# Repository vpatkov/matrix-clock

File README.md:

# Matrix Clock with Weather Station

Not too small, not too big, auto-syncing clock with wide viewing angle,
pretty bright at sunny day and not too bright at night, having a
simple weather station, without any wires except a Micro-USB power.

- Show clock, outdoor and indoor temperatures, indoor relative humidity, and
  atmospheric pressure
- Show the peak values and the change of any weather parameter for 24 hours
- Clock is wirelessly synced with a PC and maintained when the PC is offline
- Automatic brightness control
- Intuitively controlled with a single clickable rotary encoder on the back side

The project includes a base station with a LED matrix display, and two
wireless modules: one is for measuring outdoor temperature, and one is for
communication with a PC (syncing time).

If, for some reason, the base station conclude that some data is unreliable, it
show the latest reliable data with a warning mark as a point in the bottom
right corner. Clock is unreliable if not synced with a PC for a week. Outdoor
temperature is unreliable if no data was received from the outdoor sensor for
10 minutes. Data from indoor sensors is unreliable in case of any error.

If the battery in the outdoor module is low, a warning mark as a point in
the top right corner appears on the outdoor temperature screen.

It's a project I made for personal use in 2014 with some updates then.
It's based on my own preferences and ad hoc decisions. Also, it's my first
real-world electronic project after "LED blinking", and so have many design
lacks.

## Technical details

The base station is a sandwich of two boards called in sources as `base` and
`matrix`. The `base` board contains an MCU, indoor sensors, RF module, and other
peripherals. The `matrix` board is just a SPI controlled 24×8 LED matrix.

The wireless modules are called in sources as `outdoor` (outdoor temperature
measurement) and `pc-link` (communication with a PC). The `pc-link` module
is connected to a PC by USB, and appears as a virtual serial port (CP2102N chip
is used for that). CP2102N also feeds 1 MHz clock to the MCU, the chip
must be configured for that with Silabs' [configuration tool](https://www.silabs.com/products/development-tools/software/simplicity-studio).
The `pc-link` module is controlled by a host program `matrix-clock` (in the
`software` directory). Currently, the program is used just for sending
current time to the base station (add it to cron).

The wireless network is build on Nordic NRF24L01+ chips.

The front and rear glasses for the base station are made in
[Ponoko](https://www.ponoko.com/) by laser cutting from "acrylic gray tint"
material using the `case/base-station.svg` file.

The case for the outdoor module is 3D printed from the `case/outdoor-case.stl`
and `case/outdoor-cover.stl` files.

## License

Creative Commons Zero 1.0

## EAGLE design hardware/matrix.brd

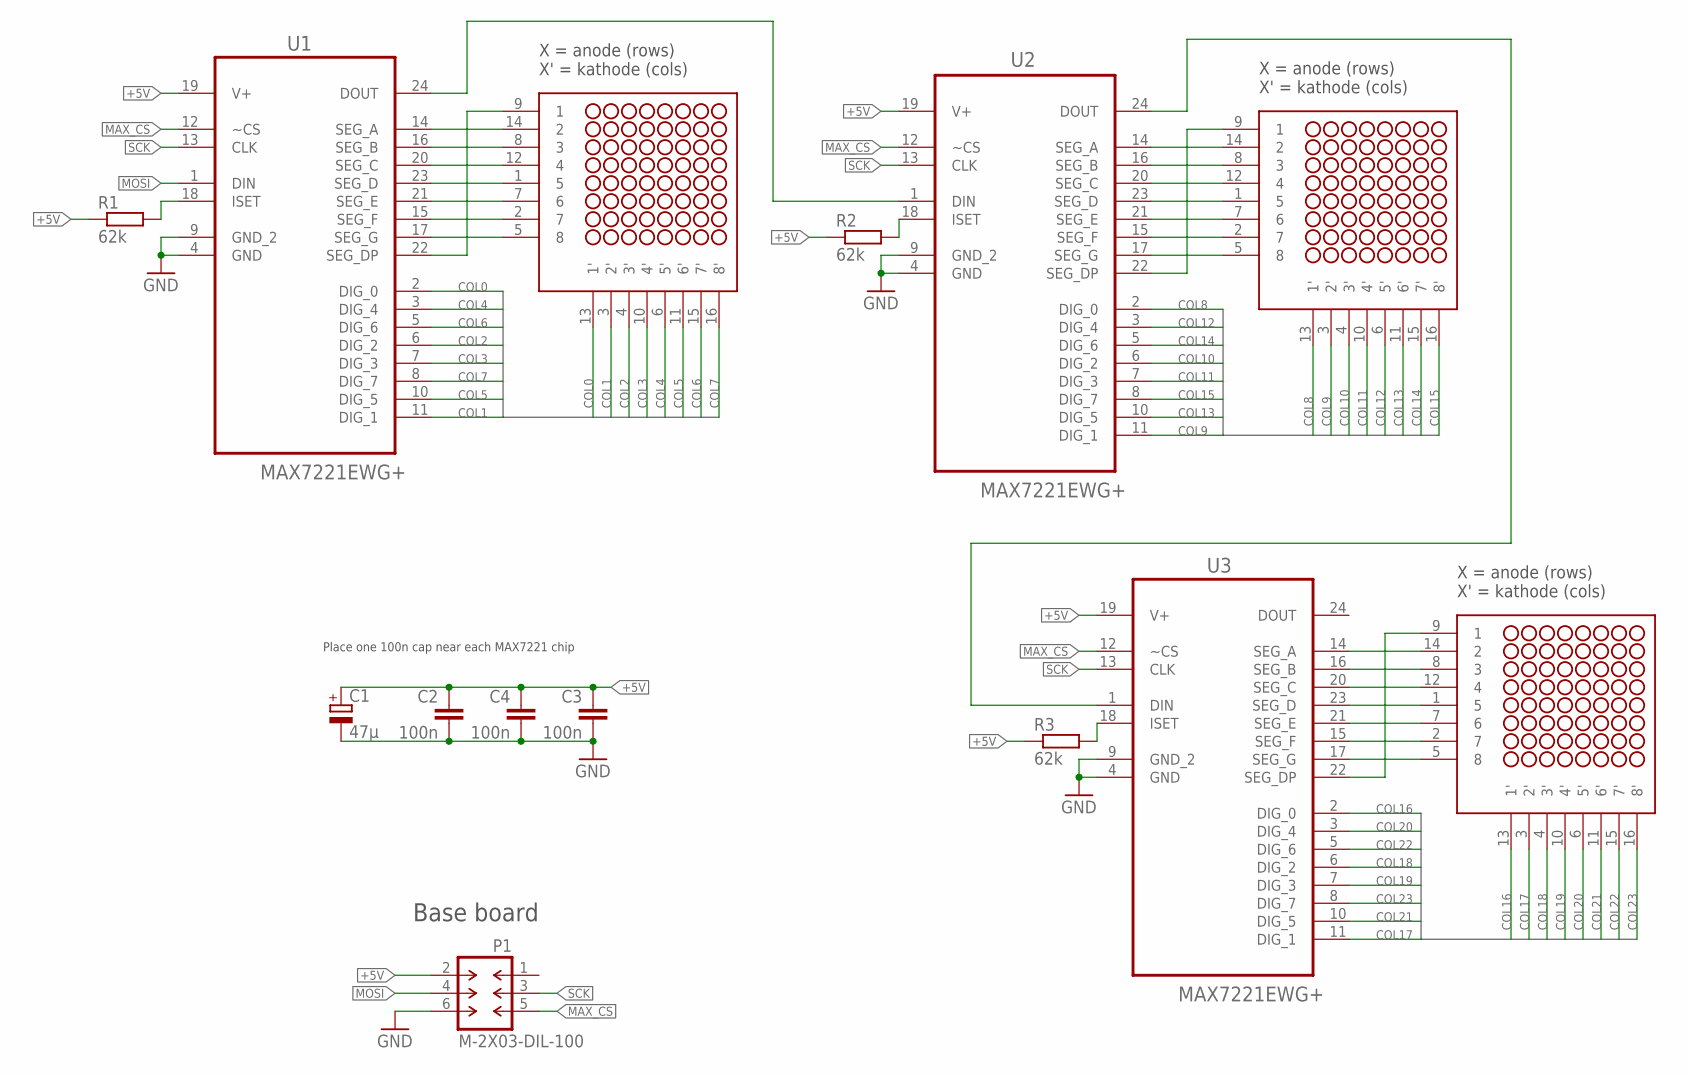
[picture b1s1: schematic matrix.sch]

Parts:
C1: 47μ; D/7343-31W
C2, C3, C4: 100n; C1206
M1, M2, M3: 1088BS; NFM-12881BG-11
P1: M-2X03-DIL-100; DIL-100-2X03
R1, R2, R3: 62k; R1206
U1, U2, U3: MAX7221EWG+; SOIC127P1032X265-24N

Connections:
+5V: C1.+, C2.1, C3.1, C4.1, P1.2, R1.1, R2.1, R3.1, U1.19 (V+), U2.19 (V+), U3.19 (V+)
COL0: M1.13 (1'), U1.2 (DIG_0)
COL1: M1.3 (2'), U1.11 (DIG_1)
COL2: M1.4 (3'), U1.6 (DIG_2)
COL3: M1.10 (4'), U1.7 (DIG_3)
COL4: M1.6 (5'), U1.3 (DIG_4)
COL5: M1.11 (6'), U1.10 (DIG_5)
COL6: M1.15 (7'), U1.5 (DIG_6)
COL7: M1.16 (8'), U1.8 (DIG_7)
COL8: M2.13 (1'), U2.2 (DIG_0)
COL9: M2.3 (2'), U2.11 (DIG_1)
COL10: M2.4 (3'), U2.6 (DIG_2)
COL11: M2.10 (4'), U2.7 (DIG_3)
COL12: M2.6 (5'), U2.3 (DIG_4)
COL13: M2.11 (6'), U2.10 (DIG_5)
COL14: M2.15 (7'), U2.5 (DIG_6)
COL15: M2.16 (8'), U2.8 (DIG_7)
COL16: M3.13 (1'), U3.2 (DIG_0)
COL17: M3.3 (2'), U3.11 (DIG_1)
COL18: M3.4 (3'), U3.6 (DIG_2)
COL19: M3.10 (4'), U3.7 (DIG_3)
COL20: M3.6 (5'), U3.3 (DIG_4)
COL21: M3.11 (6'), U3.10 (DIG_5)
COL22: M3.15 (7'), U3.5 (DIG_6)
COL23: M3.16 (8'), U3.8 (DIG_7)
GND: C1.-, C2.2, C3.2, C4.2, P1.6, U1.4 (GND), U1.9 (GND_2), U2.4 (GND), U2.9 (GND_2), U3.4 (GND), U3.9 (GND_2)
MAX_CS: P1.5, U1.12 (~CS), U2.12 (~CS), U3.12 (~CS)
MOSI: P1.4, U1.1 (DIN)
unnamed: M1.9 (1), U1.22 (SEG_DP)
unnamed: M1.5 (8), U1.17 (SEG_G)
unnamed: M1.2 (7), U1.15 (SEG_F)
unnamed: M1.7 (6), U1.21 (SEG_E)
unnamed: M1.1 (5), U1.23 (SEG_D)
unnamed: M1.12 (4), U1.20 (SEG_C)
unnamed: M1.8 (3), U1.16 (SEG_B)
unnamed: M1.14 (2), U1.14 (SEG_A)
unnamed: M2.9 (1), U2.22 (SEG_DP)
unnamed: M2.14 (2), U2.14 (SEG_A)
unnamed: M2.8 (3), U2.16 (SEG_B)
unnamed: M2.12 (4), U2.20 (SEG_C)
unnamed: M2.1 (5), U2.23 (SEG_D)
unnamed: M2.7 (6), U2.21 (SEG_E)
unnamed: M2.2 (7), U2.15 (SEG_F)
unnamed: M2.5 (8), U2.17 (SEG_G)
unnamed: M3.9 (1), U3.22 (SEG_DP)
unnamed: M3.5 (8), U3.17 (SEG_G)
unnamed: M3.2 (7), U3.15 (SEG_F)
unnamed: M3.7 (6), U3.21 (SEG_E)
unnamed: M3.1 (5), U3.23 (SEG_D)
unnamed: M3.12 (4), U3.20 (SEG_C)
unnamed: M3.8 (3), U3.16 (SEG_B)
unnamed: M3.14 (2), U3.14 (SEG_A)
unnamed: U1.24 (DOUT), U2.1 (DIN)
unnamed: U2.24 (DOUT), U3.1 (DIN)
unnamed: R1.2, U1.18 (ISET)
unnamed: R2.2, U2.18 (ISET)
unnamed: R3.2, U3.18 (ISET)
SCK: P1.3, U1.13 (CLK), U2.13 (CLK), U3.13 (CLK)

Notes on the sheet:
X = anode (rows) X' = kathode (cols)
Base board
Place one 100n cap near each MAX7221 chip

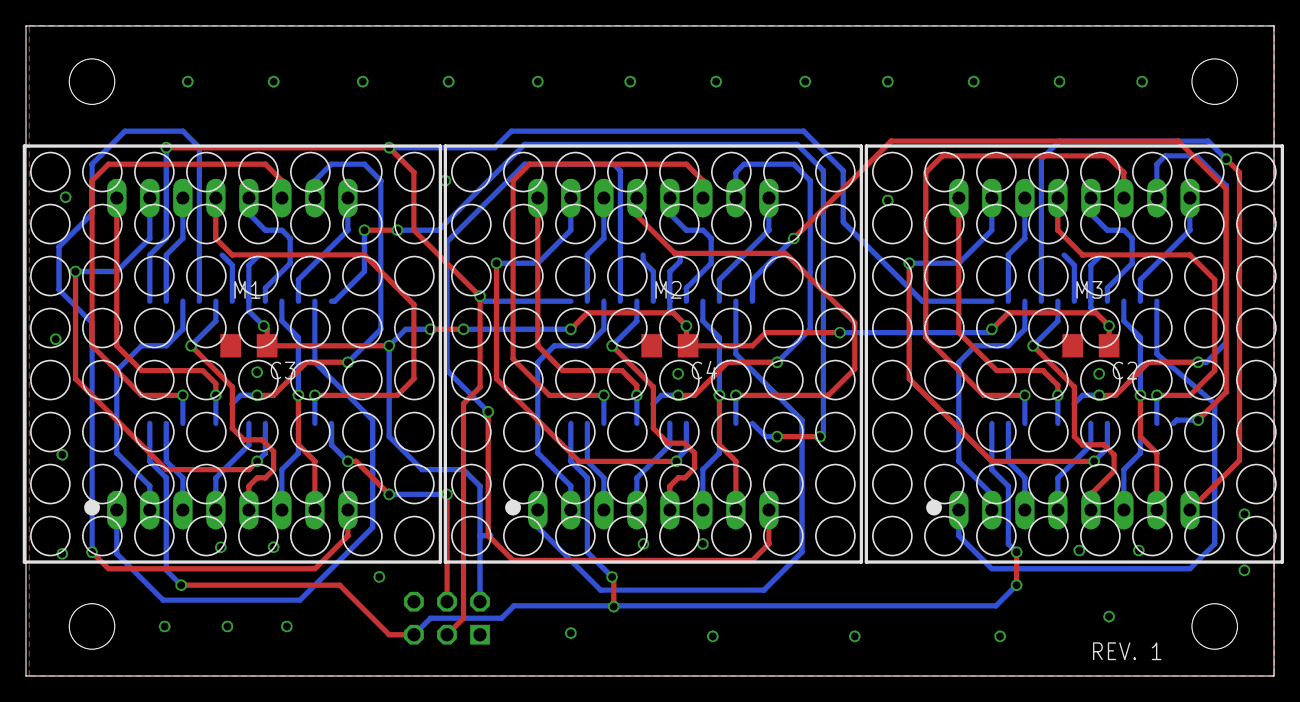
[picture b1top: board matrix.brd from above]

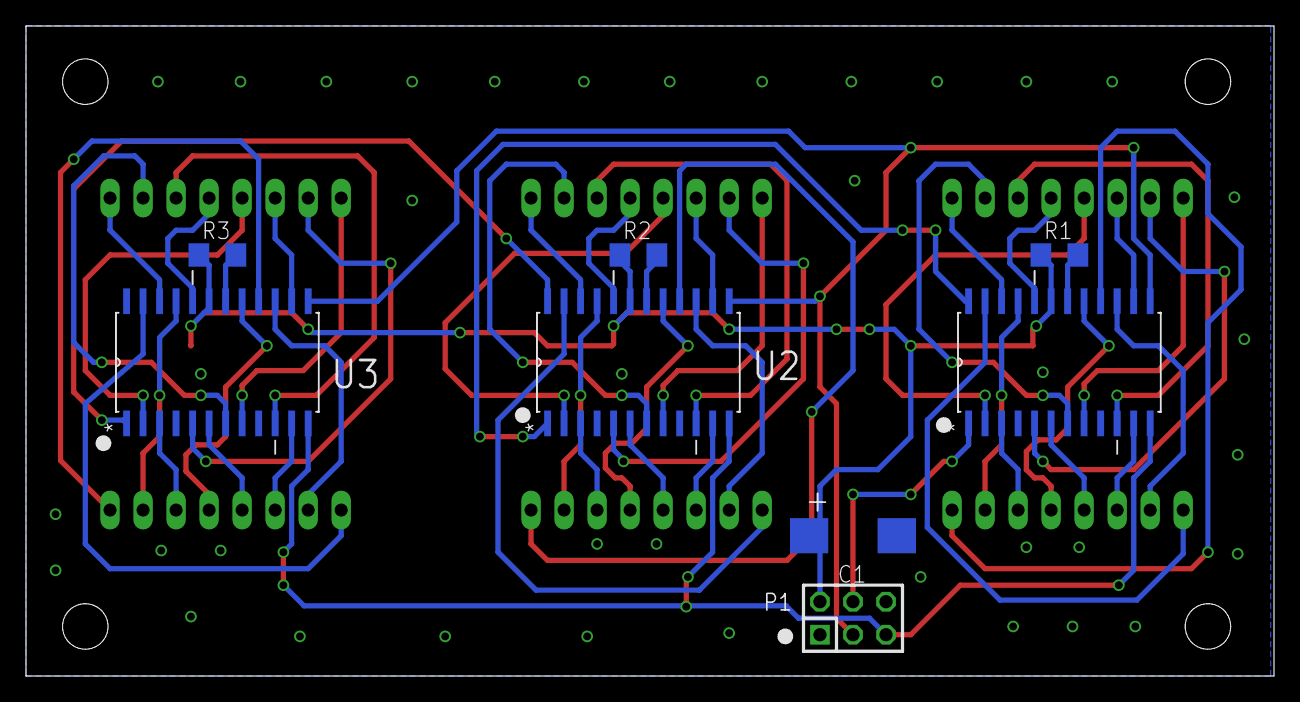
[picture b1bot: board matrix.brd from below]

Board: 2 copper layers, 96.0 x 50.0 mm, 14 parts (8 on the bottom side), 58 nets.

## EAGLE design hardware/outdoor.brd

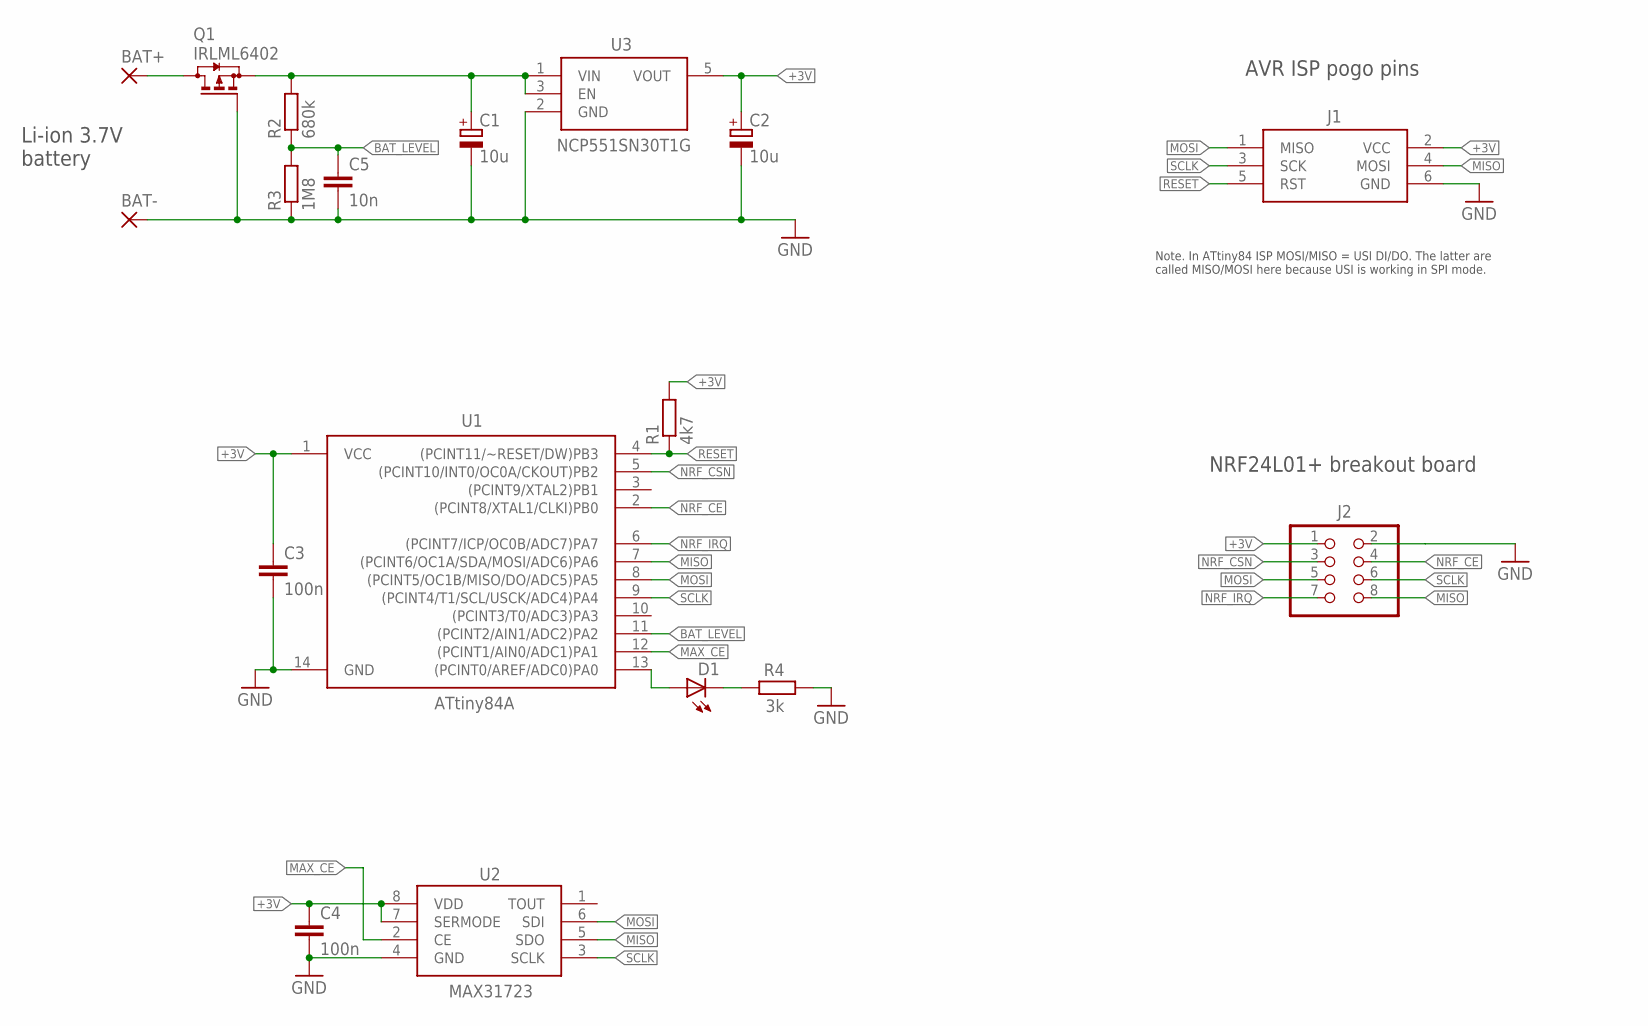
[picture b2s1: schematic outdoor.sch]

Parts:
BAT+: 2,54/1,0
BAT-: 2,54/1,0
C1, C2: 10u; CT3216
C3, C4: 100n; C0805
C5: 10n; C0805
D1: LEDSMT1206; 1206
J1: POGO_AVR_ISP6
J2: PINHD-2X4; 2X04
Q1: IRLML6402; SOT23
R1: 4k7; R0805
R2: 680k; R0805
R3: 1M8; R0805
R4: 3k; R0805
U1: ATtiny84A; SO14
U2: MAX31723; UMAX8
U3: NCP551SN30T1G; SOT23-5

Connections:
+3V: C2.+, C3.1, C4.1, J1.2 (VCC), J2.1, R1.2, U1.1 (VCC), U2.7 (SERMODE), U2.8 (VDD), U3.5 (VOUT)
BAT_LEVEL: C5.1, R2.1, R3.2, U1.11 ((PCINT2/AIN1/ADC2)PA2)
GND: BAT-.1, C1.-, C2.-, C3.2, C4.2, C5.2, J1.6 (GND), J2.2, Q1.1 (G), R3.1, R4.1, U1.14 (GND), U2.4 (GND), U3.2 (GND)
MAX_CE: U1.12 ((PCINT1/AIN0/ADC1)PA1), U2.2 (CE)
MISO: J1.4 (MOSI), J2.8, U1.7 ((PCINT6/OC1A/SDA/MOSI/ADC6)PA6), U2.5 (SDO)
MOSI: J1.1 (MISO), J2.5, U1.8 ((PCINT5/OC1B/MISO/DO/ADC5)PA5), U2.6 (SDI)
unnamed: BAT+.1, Q1.3 (D)
unnamed: C1.+, Q1.2 (S), R2.2, U3.1 (VIN), U3.3 (EN)
unnamed: D1.A, U1.13 ((PCINT0/AREF/ADC0)PA0)
unnamed: D1.C, R4.2
NRF_CE: J2.4, U1.2 ((PCINT8/XTAL1/CLKI)PB0)
NRF_CSN: J2.3, U1.5 ((PCINT10/INT0/OC0A/CKOUT)PB2)
NRF_IRQ: J2.7, U1.6 ((PCINT7/ICP/OC0B/ADC7)PA7)
RESET: J1.5 (RST), R1.1, U1.4 ((PCINT11/~RESET/DW)PB3)
SCLK: J1.3 (SCK), J2.6, U1.9 ((PCINT4/T1/SCL/USCK/ADC4)PA4), U2.3 (SCLK)

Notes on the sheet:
Li-ion 3.7V battery
Note. In ATtiny84 ISP MOSI/MISO = USI DI/DO. The latter are called MISO/MOSI here because USI is working in SPI mode.
AVR ISP pogo pins
NRF24L01+ breakout board

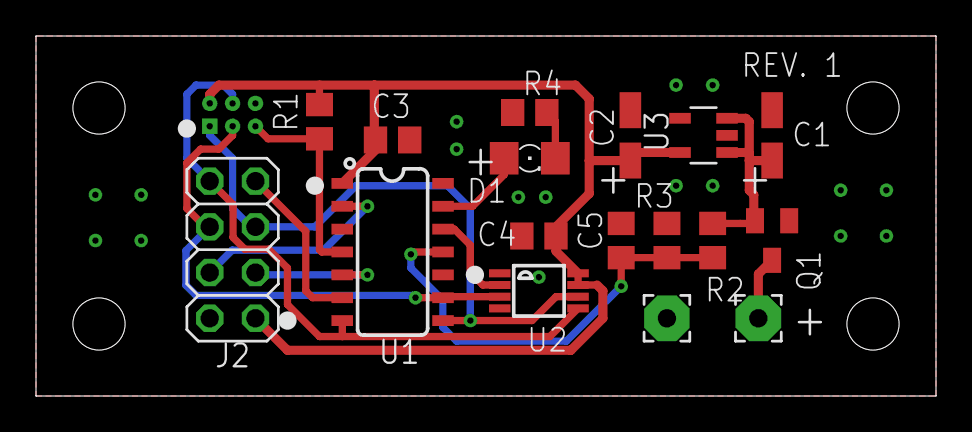
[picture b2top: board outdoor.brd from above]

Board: 2 copper layers, 50.0 x 20.0 mm, 18 parts (0 on the bottom side), 15 nets.

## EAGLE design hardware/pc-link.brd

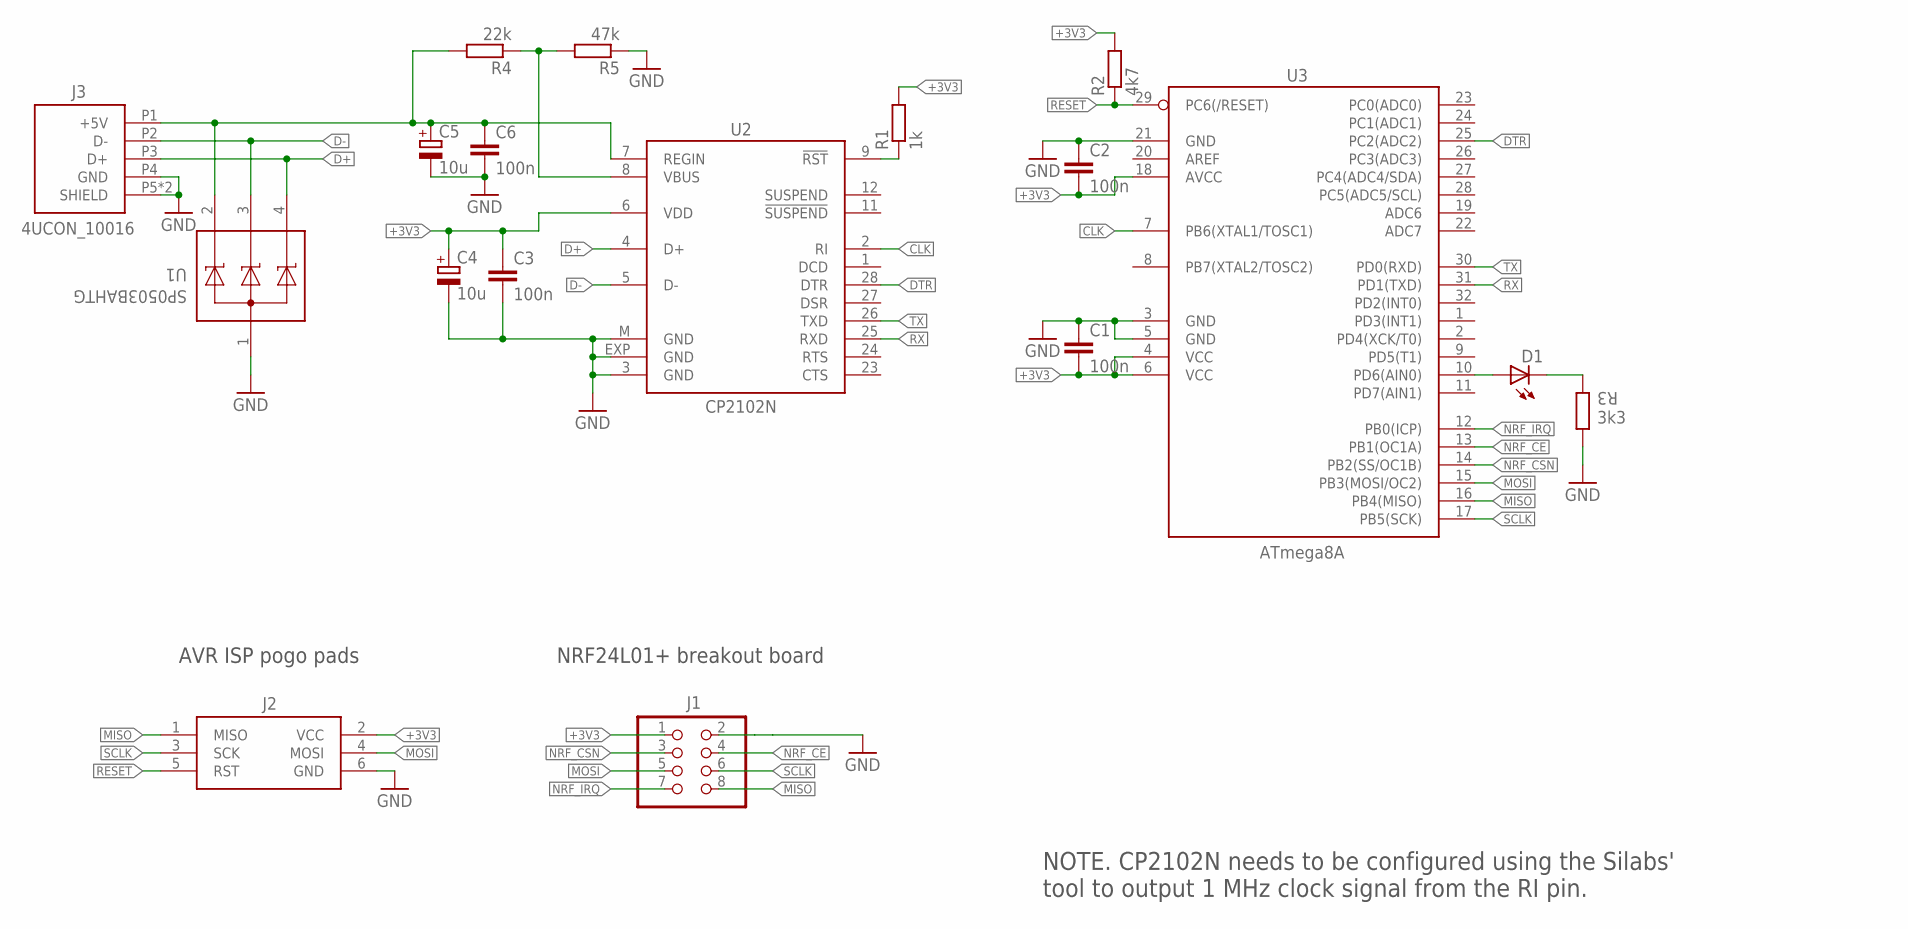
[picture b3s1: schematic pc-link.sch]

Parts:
C1, C2, C3, C6: 100n; C0805
C4, C5: 10u; CT3216
D1: LEDSMT1206; 1206
J1: PINHD-2X4; 2X04
J2: POGO_AVR_ISP6
J3: 4UCON_10016; USB_A_4UCON_10016
R1: 1k; R0805
R2: 4k7; R0805
R3: 3k3; R0805
R4: 22k; R0805
R5: 47k; R0805
U1: SP0503BAHTG; SOT143
U2: CP2102N; MLP28
U3: ATmega8A; TQFP32-08

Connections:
+3V3: C1.2, C2.2, C3.1, C4.+, J1.1, J2.2 (VCC), R1.2, R2.2, U2.6 (VDD), U3.4 (VCC), U3.6 (VCC), U3.18 (AVCC)
+5V: C5.+, C6.1, J3.P1 (+5V), R4.2, U1.2, U2.7 (REGIN)
CLK: U2.2 (RI), U3.7 (PB6(XTAL1/TOSC1))
D+: J3.P3 (D+), U1.4, U2.4 (D+)
D-: J3.P2 (D-), U1.3, U2.5 (D-)
DTR: U2.28 (DTR), U3.25 (PC2(ADC2))
GND: C1.1, C2.1, C3.2, C4.-, C5.-, C6.2, J1.2, J2.6 (GND), J3.P4 (GND), J3.P5 (SHIELD), J3.P6 (SHIELD), R3.1, R5.1, U1.1, U2.3 (GND), U2.EXP (GND), U2.M (GND), U3.3 (GND), U3.5 (GND), U3.21 (GND)
MISO: J1.8, J2.1 (MISO), U3.16 (PB4(MISO))
MOSI: J1.5, J2.4 (MOSI), U3.15 (PB3(MOSI/OC2))
unnamed: R1.1, U2.9 (!RST)
unnamed: D1.C, R3.2
unnamed: D1.A, U3.10 (PD6(AIN0))
unnamed: R4.1, R5.2, U2.8 (VBUS)
NRF_CE: J1.4, U3.13 (PB1(OC1A))
NRF_CSN: J1.3, U3.14 (PB2(SS/OC1B))
NRF_IRQ: J1.7, U3.12 (PB0(ICP))
RESET: J2.5 (RST), R2.1, U3.29 (PC6(/RESET))
RX: U2.25 (RXD), U3.31 (PD1(TXD))
SCLK: J1.6, J2.3 (SCK), U3.17 (PB5(SCK))
TX: U2.26 (TXD), U3.30 (PD0(RXD))

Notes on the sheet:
NOTE. CP2102N needs to be configured using the Silabs' tool to output 1 MHz clock signal from the RI pin.
NRF24L01+ breakout board
AVR ISP pogo pads

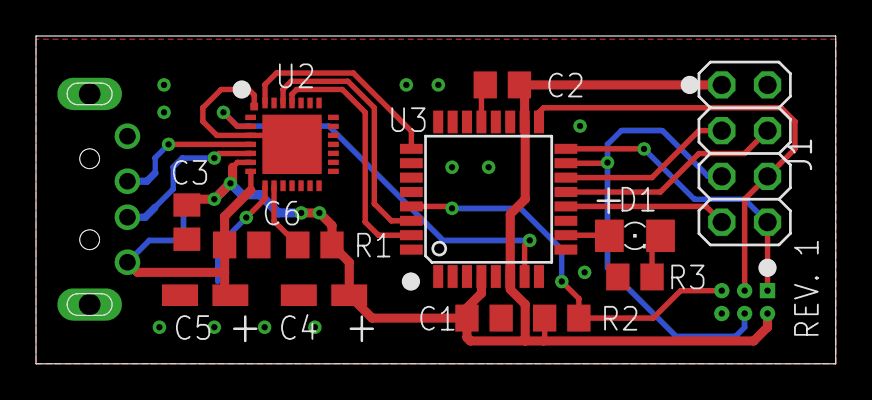
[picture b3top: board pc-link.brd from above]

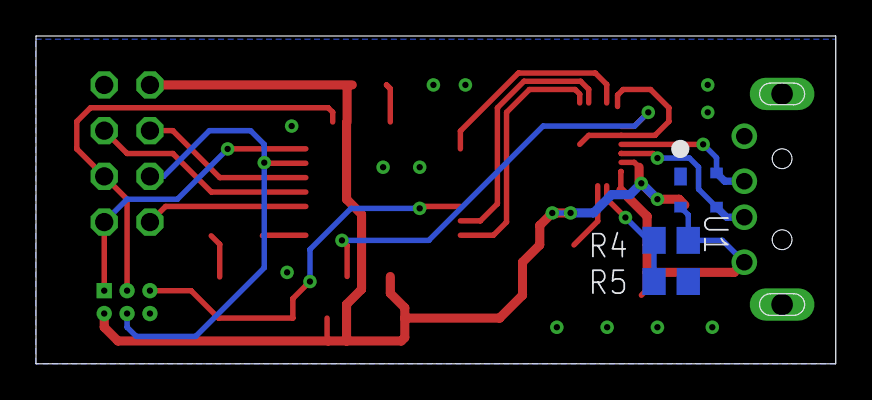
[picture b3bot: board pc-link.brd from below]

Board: 2 copper layers, 44.4 x 18.2 mm, 18 parts (3 on the bottom side), 20 nets.

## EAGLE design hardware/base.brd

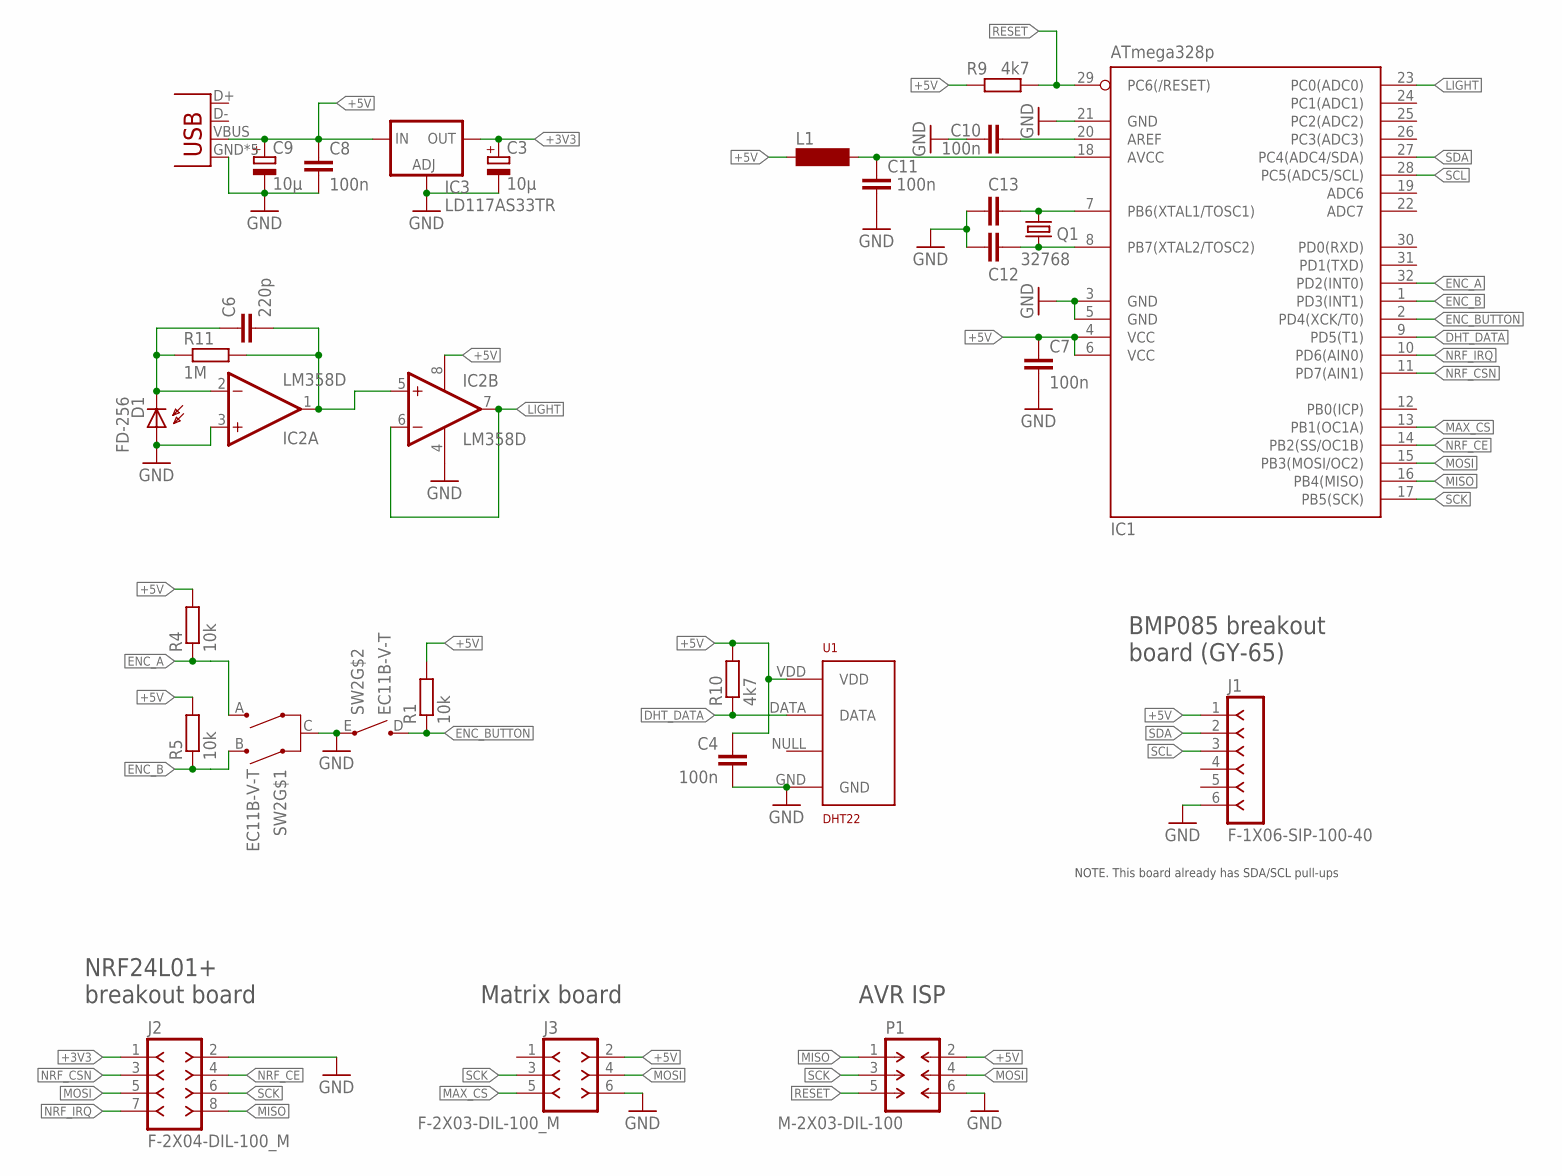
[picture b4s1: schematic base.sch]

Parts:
C3, C9: 10μ; D/7343-31R
C4, C8: 100n; C1206
C6: 220p; C1206
C7, C10, C11: 100n; C0805
C12, C13: C-EUC0805; C0805
D1: FD-256; BPX65
IC1: ATmega328p; TQFP32-08
IC2: LM358D; SO08
IC3: LD117AS33TR; SOT223
J1: F-1X06-SIP-100-40; SIP-100-06-40
J2: F-2X04-DIL-100_M; DIL-100-2X04_M
J3: F-2X03-DIL-100_M; DIL-100-2X03_M
JP5: USB-MICROB
L1: SM-1206
P1: M-2X03-DIL-100; DIL-100-2X03
Q1: 32768; TC26H
R1, R4, R5: 10k; R1206
R9, R10: 4k7; R1206
R11: 1M; R1206
SW2: EC11B-V-T; EC11B-V
U1: DHT22; RHT03_DHT-22/RA

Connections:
+3V3: C3.+, IC3.4 (OUT), J2.1
+5V: C4.1, C7.1, C8.1, C9.+, IC1.4 (VCC), IC1.6 (VCC), IC2.8 (V+), IC3.3 (IN), J1.1, J3.2, JP5.VBUS, L1.1, P1.2, R1.2, R4.2, R5.2, R9.2, R10.2, U1.VDD
DHT_DATA: IC1.9 (PD5(T1)), R10.1, U1.DATA
ENC_A: IC1.32 (PD2(INT0)), R4.1, SW2.A
ENC_B: IC1.1 (PD3(INT1)), R5.1, SW2.B
ENC_BUTTON: IC1.2 (PD4(XCK/T0)), R1.1, SW2.D
GND: C3.-, C4.2, C7.2, C8.2, C9.-, C10.2, C11.2, C12.2, C13.2, D1.A, IC1.3 (GND), IC1.5 (GND), IC1.21 (GND), IC2.3 (+IN), IC2.4 (V-), IC3.1 (ADJ), J1.6, J2.2, J3.6, JP5.GND, JP5.MT1 (GND), JP5.MT2 (GND), JP5.P$1 (GND), JP5.P$2 (GND), P1.6, SW2.C, SW2.E, U1.GND
LIGHT: C6.2, IC1.23 (PC0(ADC0)), IC2.1 (OUT), IC2.5 (+IN), IC2.6 (-IN), IC2.7 (OUT), R11.2
MAX_CS: IC1.13 (PB1(OC1A)), J3.5
MISO: IC1.16 (PB4(MISO)), J2.8, P1.1
MOSI: IC1.15 (PB3(MOSI/OC2)), J2.5, J3.4, P1.4
unnamed: C10.1, IC1.20 (AREF)
unnamed: C6.1, D1.K (C), IC2.2 (-IN), R11.1
unnamed: C11.1, IC1.18 (AVCC), L1.2
unnamed: C12.1, IC1.8 (PB7(XTAL2/TOSC2)), Q1.1
unnamed: C13.1, IC1.7 (PB6(XTAL1/TOSC1)), Q1.2
NRF_CE: IC1.14 (PB2(SS/OC1B)), J2.4
NRF_CSN: IC1.11 (PD7(AIN1)), J2.3
NRF_IRQ: IC1.10 (PD6(AIN0)), J2.7
RESET: IC1.29 (PC6(/RESET)), P1.5, R9.1
SCK: IC1.17 (PB5(SCK)), J2.6, J3.3, P1.3
SCL: IC1.28 (PC5(ADC5/SCL)), J1.3
SDA: IC1.27 (PC4(ADC4/SDA)), J1.2

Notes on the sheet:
BMP085 breakout board (GY-65)
NRF24L01+ breakout board
AVR ISP
Matrix board
NOTE. This board already has SDA/SCL pull-ups

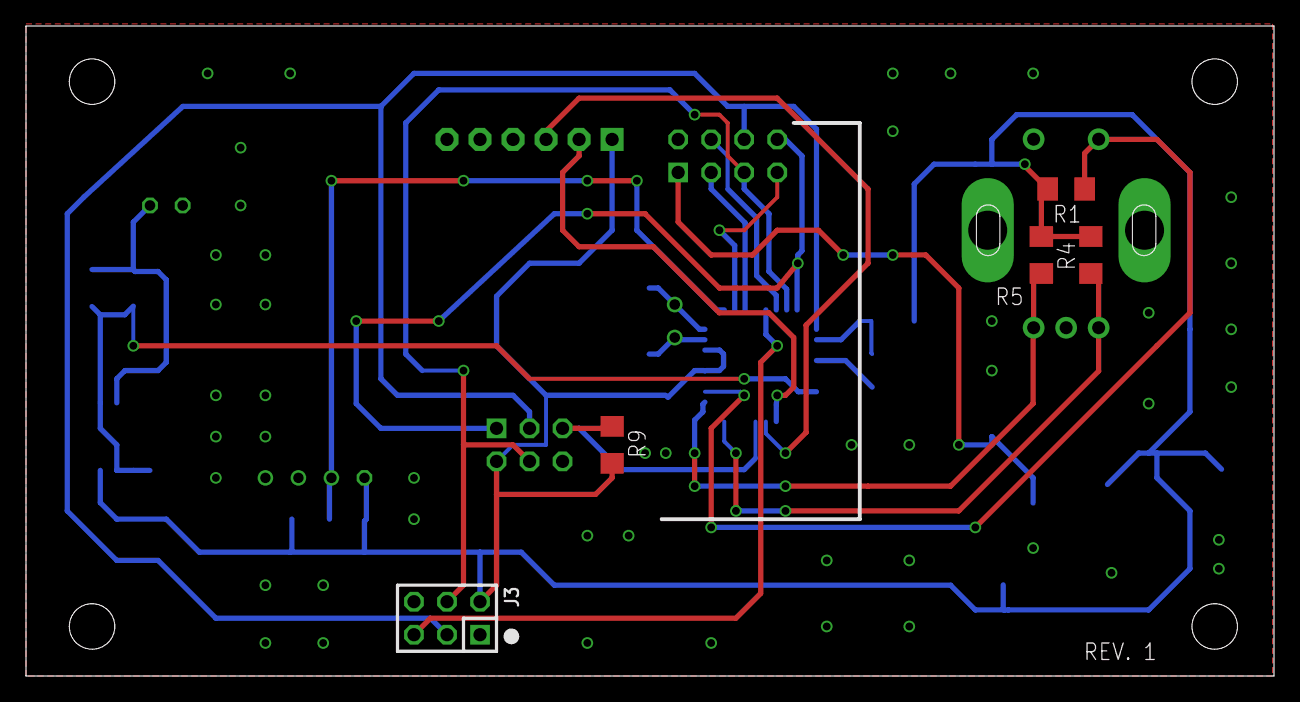
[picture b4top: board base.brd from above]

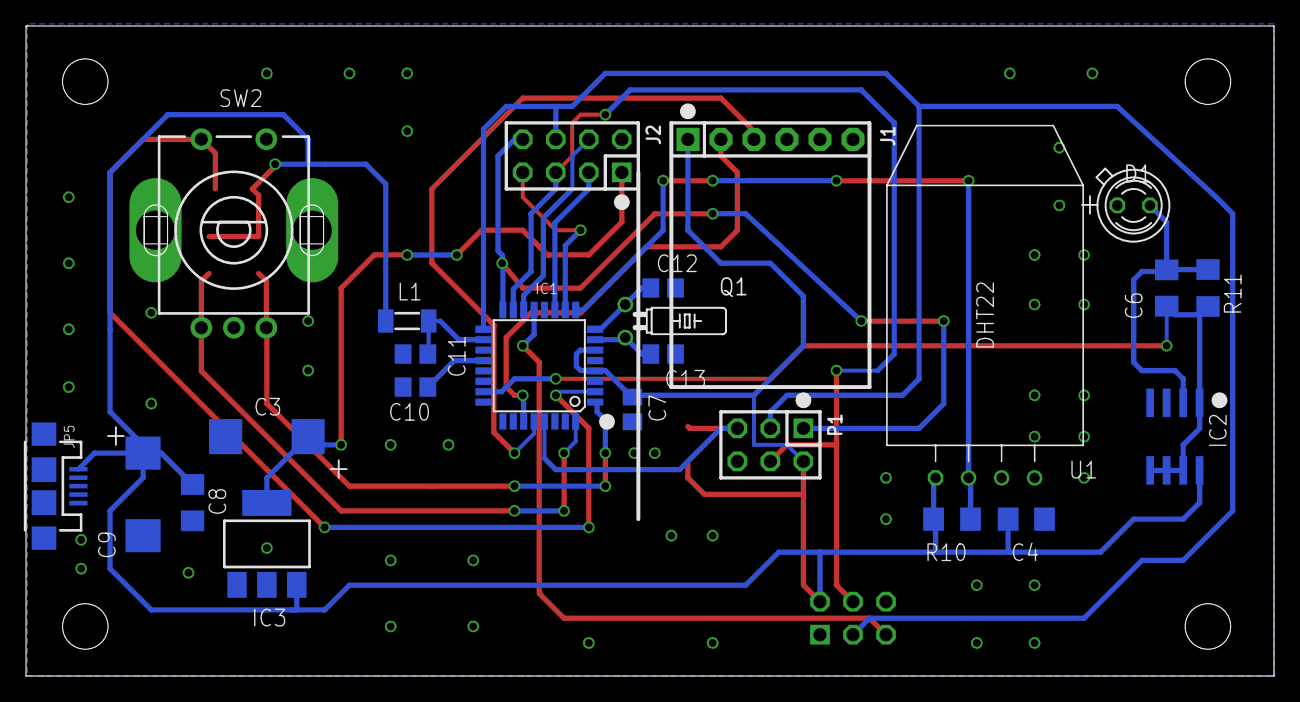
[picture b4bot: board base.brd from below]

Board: 2 copper layers, 96.0 x 50.0 mm, 29 parts (24 on the bottom side), 23 nets.

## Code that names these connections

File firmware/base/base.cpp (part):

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/* Peripherals are configured for 8 MHz system clock */
static_assert(F_CPU == 8e6, "");

constexpr Gpio::Pin max_cs = Gpio::B1;
constexpr Gpio::Pin nrf_csn = Gpio::D7, nrf_ce = Gpio::B2, nrf_irq = Gpio::D6;
constexpr Gpio::Pin dht_data = Gpio::D5;
constexpr Gpio::Pin enc_a = Gpio::D2, enc_b = Gpio::D3, enc_button = Gpio::D4;
constexpr Gpio::Pin mosi = Gpio::B3, miso = Gpio::B4, sck = Gpio::B5;

constexpr uint8_t light_adc_channel = 0;

constexpr uint32_t i2c_freq = 200e3;        /* I2C frequency (Hz) */

constexpr uint8_t full_brightness = 160;    /* Ambient light level for full matrix brightness (0..255) */
constexpr uint8_t hysteresis = 16;          /* Hysteresis of the automatic brightness control (0..255) */

constexpr int32_t outdoor_reliable_time = 10*60;        /* How long the outdoor temperature is reliable (s) */
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        {
                static uint8_t cnt = 0;
                static bool prev_state = 1;
                if (Gpio::read(enc_a) != prev_state) {
                        if (++cnt > 1) {
                                if (prev_state != 0) {  /* Negative edge */
                                        if (Gpio::read(enc_b))
                                                s_flags.enc_rotated_left = 1;
                                        else
                                                s_flags.enc_rotated_right = 1;
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        }

        /* NRF24 interrupt */
        if (Gpio::read(nrf_irq) == 0)
                s_flags.nrf24_irq = 1;
        
        /* Ambient light level */
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
                /* Rotate screens */
                if (flags.enc_rotated_left || flags.enc_rotated_right) {
                        if (Gpio::read(enc_button)) {
                                constexpr auto n = static_cast<uint8_t>(ScreenX::nr_screens);
                                const auto i = static_cast<uint8_t>(screen.x);
                                screen.x = static_cast<ScreenX>(
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
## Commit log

2019-05-09 Cosmetic
2021-06-12 printf bugfixes, etc.
2021-10-01 No daemon, use cron

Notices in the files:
parts and their libraries:
con-headers-jp: Copyright (C) 2008, Bob Starr
SparkFun-Connectors: Licensing: Creative Commons ShareAlike 4.0 International - https://creativecommons.org/licenses/by-sa/4.0
display8x8: This is v1 and is licensed under the Creative Commons (Attribution-Non-Commercial-Share Alike 2.0 UK)
